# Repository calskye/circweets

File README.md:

pcb projects go here on jithub
thanks for looking over this
-cal

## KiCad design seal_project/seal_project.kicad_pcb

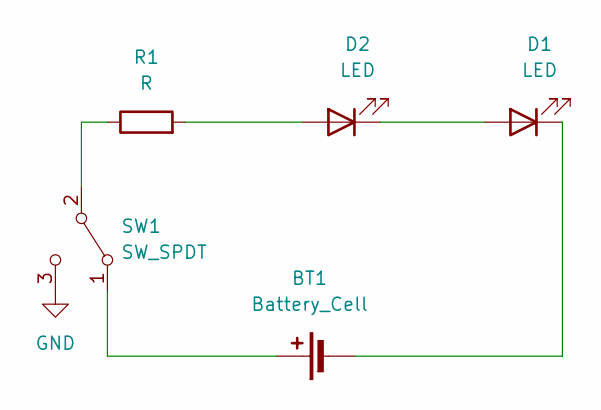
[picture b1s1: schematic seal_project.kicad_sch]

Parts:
BT1: Battery_Cell; BatteryHolder_Keystone_106_1x20mm
D1, D2: LED; LED_D5.0mm
R1: R; R_Axial_DIN0207_L6.3mm_D2.5mm_P7.62mm_Horizontal
SW1: SW_SPDT; Nidec_Copal_CAS-120A

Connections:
GND: SW1.3 (C)
unnamed: BT1.1 (+), SW1.1 (A)
unnamed: BT1.2 (-), D1.1 (K)
unnamed: D1.2 (A), D2.1 (K)
unnamed: D2.2 (A), R1.2
unnamed: R1.1, SW1.2 (B)

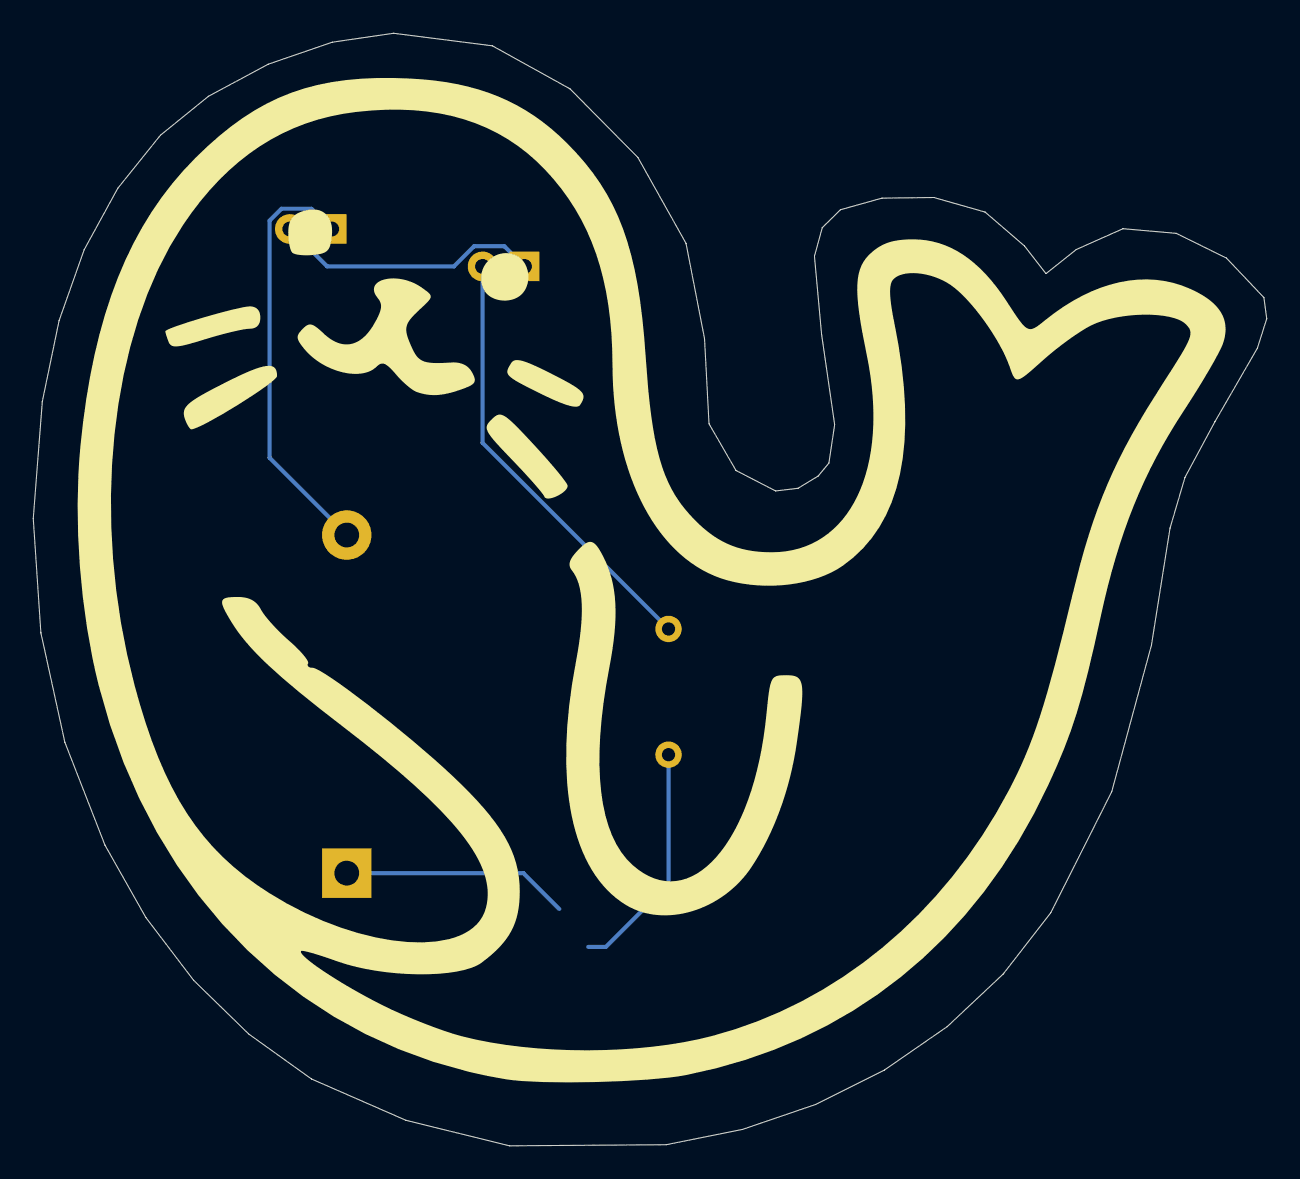
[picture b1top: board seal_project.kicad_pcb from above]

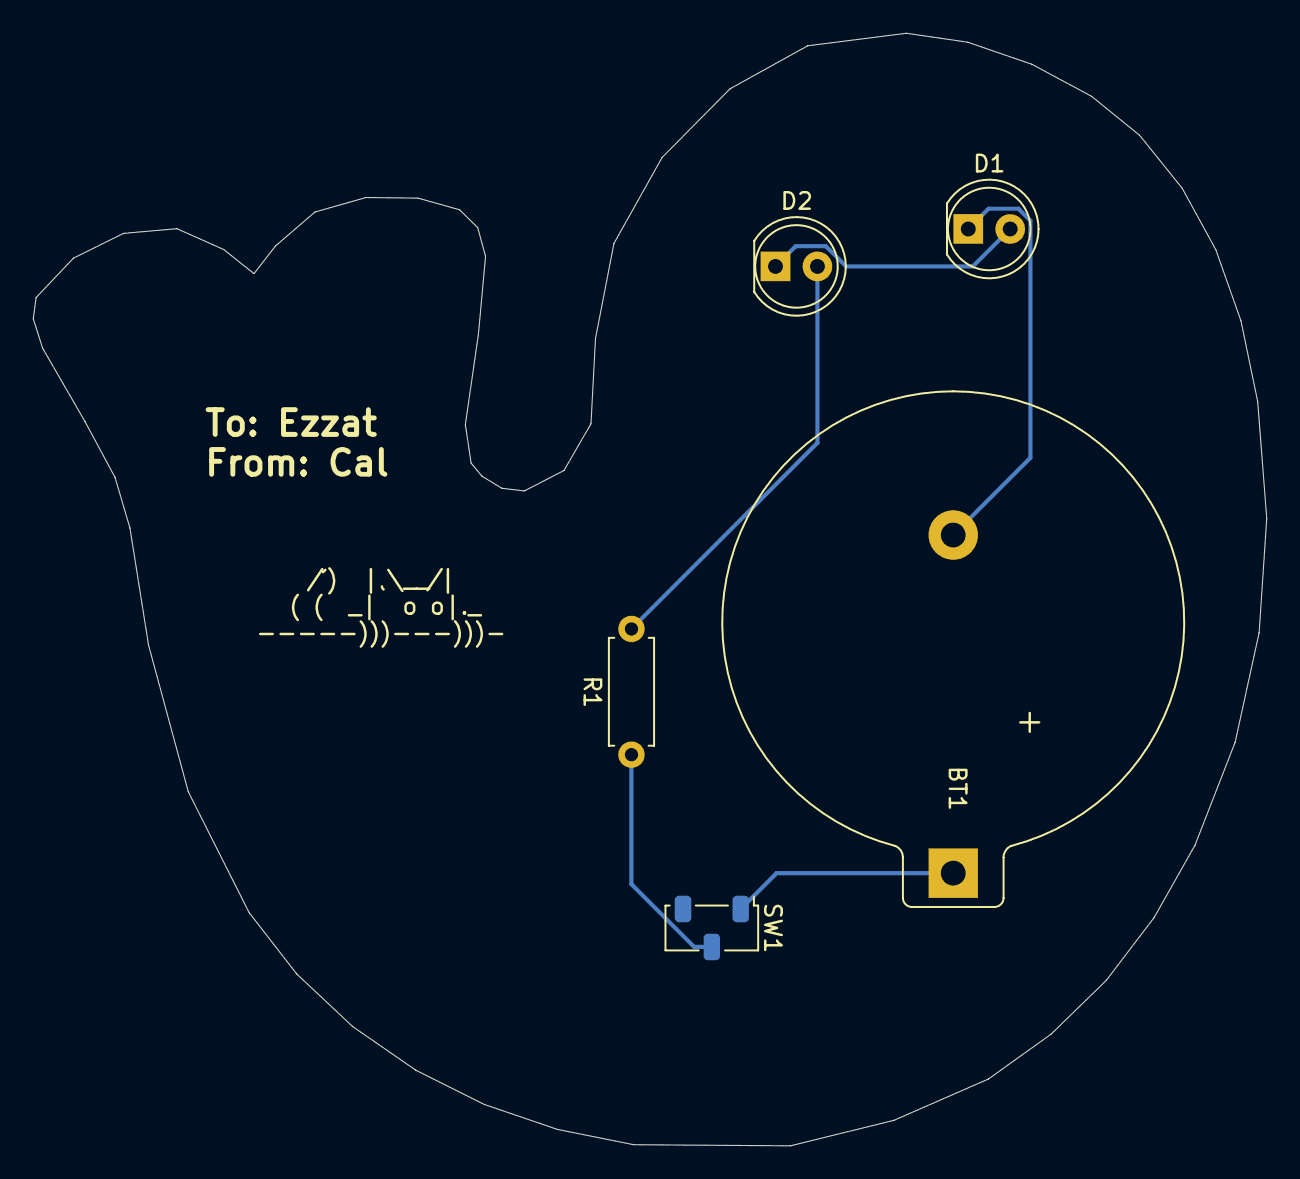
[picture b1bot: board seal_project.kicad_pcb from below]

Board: 2 copper layers, 74.8 x 67.4 mm, 5 parts (5 on the bottom side), 5 nets.

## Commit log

2025-12-15 updated files
2025-12-15 Adds
2025-12-15 Check
2025-12-15 final revisions
2025-12-16 updates, still debugging
2025-12-16 still buggy
2025-12-16 making progress
2025-12-17 done
2025-12-18 ready to fab
2025-12-18 gerber files made
